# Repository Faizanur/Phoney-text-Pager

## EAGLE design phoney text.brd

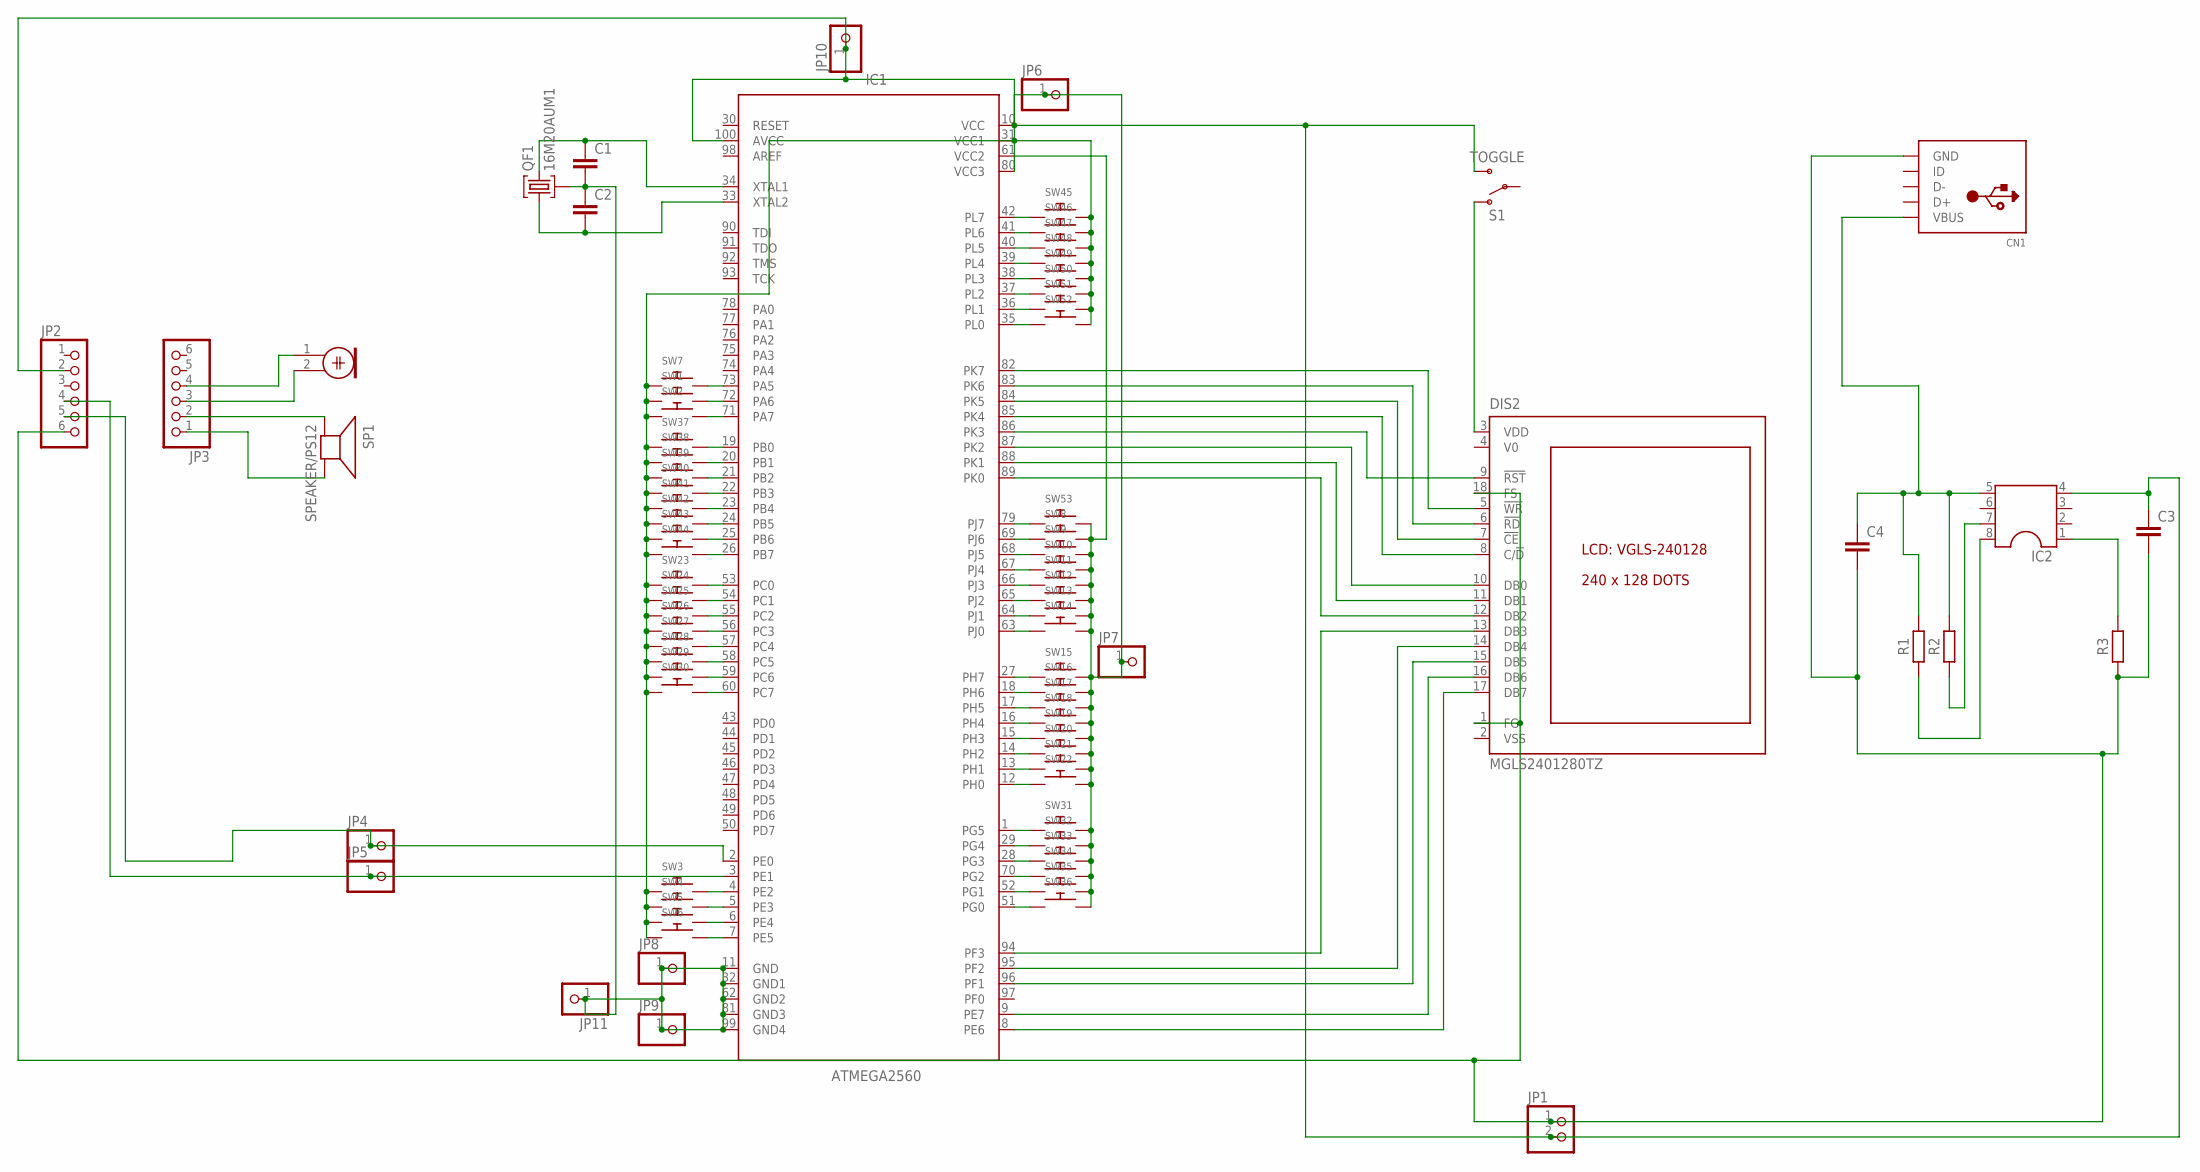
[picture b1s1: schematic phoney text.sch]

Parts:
C1, C2: C2,5-3; C2.5-3
C3, C4: C2.5/2; C2.5-2
CN1: USBMOLEX; USB-MINIB-THM-MOLEX
DIS2: MGLS2401280TZ
IC1: ATMEGA2560; QFP50P1600X1600X160-100N
IC2: DIL8; DIL08
JP1: PINHD-1X2; 1X02
JP2, JP3: PINHD-1X6CB; 1X06-CLEANBIG
JP4, JP5, JP6, JP7, JP8, JP9, JP10, JP11: PINHD-1X1; 1X01
M1: ELECTRET_MICROPHON-F6050AP; F6050AP
QF1: 16M20AUM1; UM1
R1, R2, R3: R_CHIP-0603(1608-METRIC); RESC1608X60
S1: TOGGLE; SWITCH-SPDT-PTH-8.5X3.7MM
SP1: SPEAKER/PS12; PS12
SW1, SW2, SW3, SW4, SW5, SW6, SW7, SW8, SW9, SW10, SW11, SW12, SW13, SW14, SW15, SW16, SW17, SW18, SW19, SW20, SW21, SW22, SW23, SW24, SW25, SW26, SW27, SW28, SW29, SW30, SW31, SW32, SW33, SW34, SW35, SW36, SW37, SW38, SW39, SW40, SW41, SW42, SW43, SW44, SW45, SW46, SW47, SW48, SW49, SW50, SW51, SW52, SW53: SWITCH_PUSHBUTTONSOFTTOUCHSMD_SJ; PUSHBUTTON_SMD_SJ

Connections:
unnamed: IC1.2 (PE0), JP2.5, JP4.1
unnamed: IC1.3 (PE1), JP2.4, JP5.1
unnamed: C3.1, IC1.10 (VCC), IC1.61 (VCC2), IC1.80 (VCC3), IC1.100 (AVCC), IC2.4, JP1.2, JP2.2, JP6.1, JP7.1, JP10.1, S1.3 (S), SW8.P$2, SW9.P$2, SW10.P$2, SW11.P$2, SW12.P$2, SW13.P$2, SW14.P$2, SW15.P$2, SW16.P$2, SW17.P$2, SW18.P$2, SW19.P$2, SW20.P$2, SW21.P$2, SW22.P$2, SW31.P$2, SW32.P$2, SW33.P$2, SW34.P$2, SW35.P$2, SW36.P$2, SW53.P$2
unnamed: DIS2.17 (DB7), IC1.8 (PE6)
unnamed: DIS2.12 (DB2), IC1.89 (PK0)
unnamed: DIS2.11 (DB1), IC1.88 (PK1)
unnamed: DIS2.10 (DB0), IC1.87 (PK2)
unnamed: DIS2.9 (!RST), IC1.86 (PK3)
unnamed: DIS2.8 (C/!D), IC1.85 (PK4)
unnamed: DIS2.7 (!CE), IC1.84 (PK5)
unnamed: DIS2.6 (!RD), IC1.83 (PK6)
unnamed: DIS2.5 (!WR), IC1.82 (PK7)
unnamed: IC1.73 (PA5), SW7.P$2
unnamed: IC1.72 (PA6), SW1.P$2
unnamed: IC1.71 (PA7), SW2.P$2
unnamed: IC1.19 (PB0), SW37.P$2
unnamed: IC1.20 (PB1), SW38.P$2
unnamed: IC1.21 (PB2), SW39.P$2
unnamed: IC1.22 (PB3), SW40.P$2
unnamed: IC1.23 (PB4), SW41.P$2
unnamed: IC1.24 (PB5), SW42.P$2
unnamed: IC1.25 (PB6), SW43.P$2
unnamed: IC1.26 (PB7), SW44.P$2
unnamed: IC1.53 (PC0), SW23.P$2
unnamed: IC1.54 (PC1), SW24.P$2
unnamed: IC1.55 (PC2), SW25.P$2
unnamed: IC1.56 (PC3), SW26.P$2
unnamed: IC1.57 (PC4), SW27.P$2
unnamed: IC1.58 (PC5), SW28.P$2
unnamed: IC1.59 (PC6), SW29.P$2
unnamed: IC1.60 (PC7), SW30.P$2
unnamed: IC1.69 (PJ6), SW8.P$1
unnamed: IC1.68 (PJ5), SW9.P$1
unnamed: IC1.67 (PJ4), SW10.P$1
unnamed: IC1.66 (PJ3), SW11.P$1
unnamed: IC1.65 (PJ2), SW12.P$1
unnamed: IC1.64 (PJ1), SW13.P$1
unnamed: IC1.63 (PJ0), SW14.P$1
unnamed: IC1.27 (PH7), SW15.P$1
unnamed: IC1.18 (PH6), SW16.P$1
unnamed: IC1.17 (PH5), SW17.P$1
unnamed: IC1.16 (PH4), SW18.P$1
unnamed: IC1.15 (PH3), SW19.P$1
unnamed: IC1.14 (PH2), SW20.P$1
unnamed: IC1.13 (PH1), SW21.P$1
unnamed: IC1.12 (PH0), SW22.P$1
unnamed: IC1.1 (PG5), SW31.P$1
unnamed: IC1.29 (PG4), SW32.P$1
unnamed: IC1.28 (PG3), SW33.P$1
unnamed: IC1.70 (PG2), SW34.P$1
unnamed: IC1.52 (PG1), SW35.P$1
unnamed: IC1.51 (PG0), SW36.P$1
unnamed: IC1.42 (PL7), SW45.P$1
unnamed: IC1.41 (PL6), SW46.P$1
unnamed: IC1.40 (PL5), SW47.P$1
unnamed: IC1.39 (PL4), SW48.P$1
unnamed: IC1.38 (PL3), SW49.P$1
unnamed: IC1.37 (PL2), SW50.P$1
unnamed: IC1.36 (PL1), SW51.P$1
unnamed: IC1.35 (PL0), SW52.P$1
unnamed: IC1.4 (PE2), SW3.P$2
unnamed: IC1.5 (PE3), SW4.P$2
unnamed: IC1.6 (PE4), SW5.P$2
unnamed: IC1.7 (PE5), SW6.P$2
unnamed: IC1.31 (VCC1), SW1.P$1, SW2.P$1, SW3.P$1, SW4.P$1, SW5.P$1, SW6.P$1, SW7.P$1, SW23.P$1, SW24.P$1, SW25.P$1, SW26.P$1, SW27.P$1, SW28.P$1, SW29.P$1, SW30.P$1, SW37.P$1, SW38.P$1, SW39.P$1, SW40.P$1, SW41.P$1, SW42.P$1, SW43.P$1, SW44.P$1, SW45.P$2, SW46.P$2, SW47.P$2, SW48.P$2, SW49.P$2, SW50.P$2, SW51.P$2, SW52.P$2
unnamed: IC1.79 (PJ7), SW53.P$1
unnamed: DIS2.3 (VDD), S1.1 (O)
unnamed: C1.2, C2.1, IC1.11 (GND), IC1.32 (GND1), IC1.62 (GND2), IC1.81 (GND3), IC1.99 (GND4), JP8.1, JP9.1, JP11.1, QF1.2
unnamed: C1.1, IC1.34 (XTAL1), QF1.3
unnamed: C2.2, IC1.33 (XTAL2), QF1.1
unnamed: IC2.1, R3.2
unnamed: IC2.8, R1.1
unnamed: IC2.7, R2.1
unnamed: C4.1, CN1.VBUS, IC2.5, R1.2, R2.2
unnamed: DIS2.13 (DB3), IC1.94 (PF3)
unnamed: DIS2.14 (DB4), IC1.95 (PF2)
unnamed: C3.2, C4.2, CN1.GND, DIS2.1 (FG), DIS2.18 (FS), JP1.1, JP2.6, R3.1
unnamed: JP3.1, SP1.P$2 (-)
unnamed: JP3.2, SP1.P$1 (+)
unnamed: JP3.3, M1.2
unnamed: JP3.4, M1.1
unnamed: DIS2.15 (DB5), IC1.96 (PF1)
unnamed: DIS2.16 (DB6), IC1.9 (PE7)

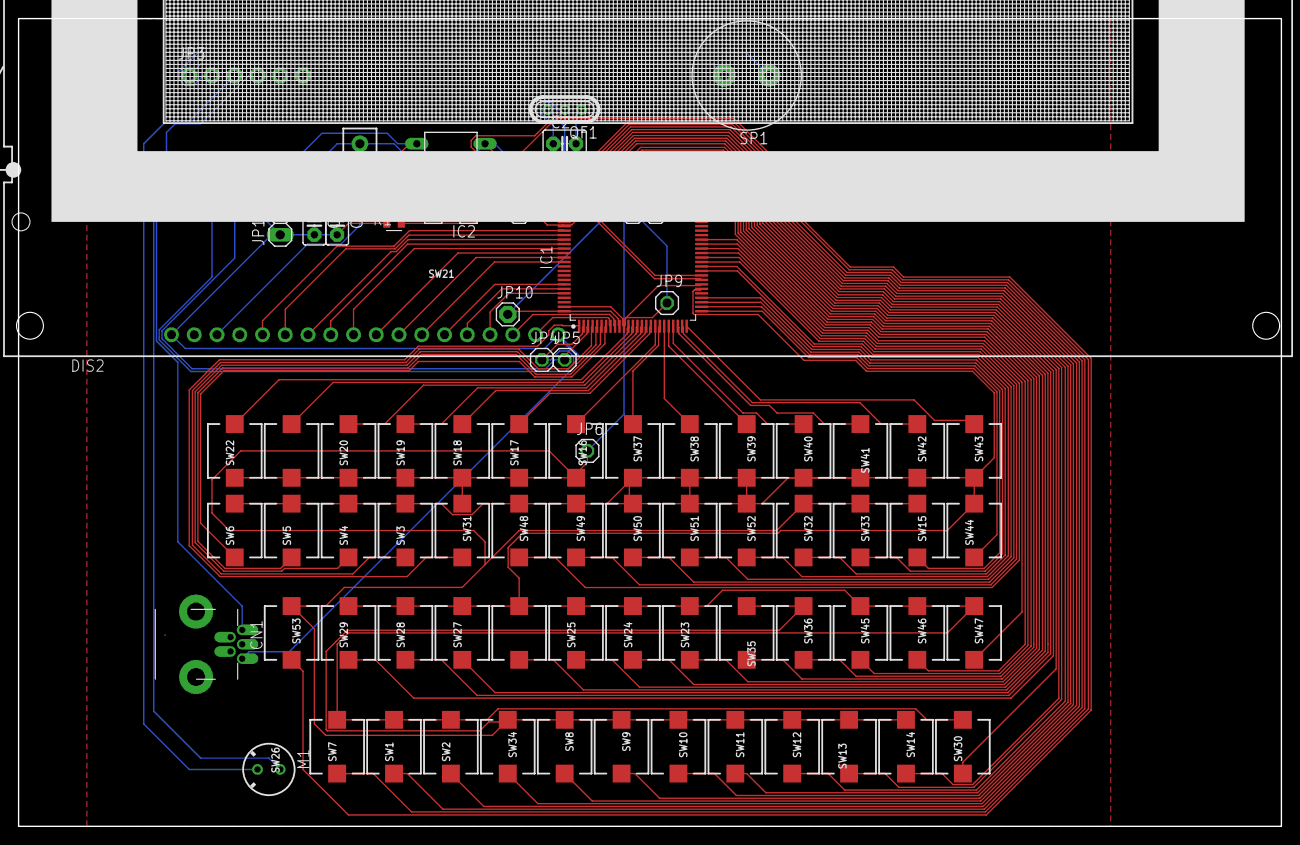
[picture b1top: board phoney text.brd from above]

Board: 2 copper layers, 141.0 x 90.2 mm, 79 parts (0 on the bottom side), 83 nets.

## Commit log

2022-08-30 Create Source Code
